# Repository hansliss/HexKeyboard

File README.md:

# HexKeyboard

A 25 x 25 keypad with a LED display and many features.

* The matrix rows are on pins 4, 12, 6, 7, 23
* The matrix columns are on pins 22, 21, 20, 19, 18

The SD card holder is connected to SPI, plus

* Card Detect = PB0 / pin 17
* Chip Enable = PB4 / pin 8

Note that CD is connected to the RXLED pin, so it will probably collide with serial data.

The display is connected like this:

* CLK = 9
* CS = 10
* DIN = 11

This requires a local max7219.h with the defines modified. Just copy 

### Serial LED pins
If you want to eliminate problems with the two LED pins (see above), you can always just disable the entire functionality, by modifying USBCore.cpp (probably found here: _C:\Users\Yourname\AppData\Local\Arduino15\packages\arduino\hardware\avr\1.8.6\cores\arduino_).

Just comment out everything to do with RXLED and TXLED, and the file will be recompiled upon the next build.

### Misc
The SPI pins for the MAX7219 display aren't actually SPI pins. Still, the max7219 library just bit-bangs the protocol so it doesn't really matter.

If you add an ESP-01/ESP-01S (with the Espressif "AT" firmware, for instance), set it to use 9600 baud
on the serial interface. The default 115200 baud seems a bit too fast.

If you print the case, and want a LED indicator for the ESP-01, print out the included wifiSign model on
a resin printer using transparent resin, then drill a 3.5mm hole roughly 3.7mm below the lower edge of the
display and 13mm to the right of the right edge of the display, insert the transparent plug, and then pour black resin carefully around the symbol (preferably using a syringe and microscope) and cure it with a UV
light.

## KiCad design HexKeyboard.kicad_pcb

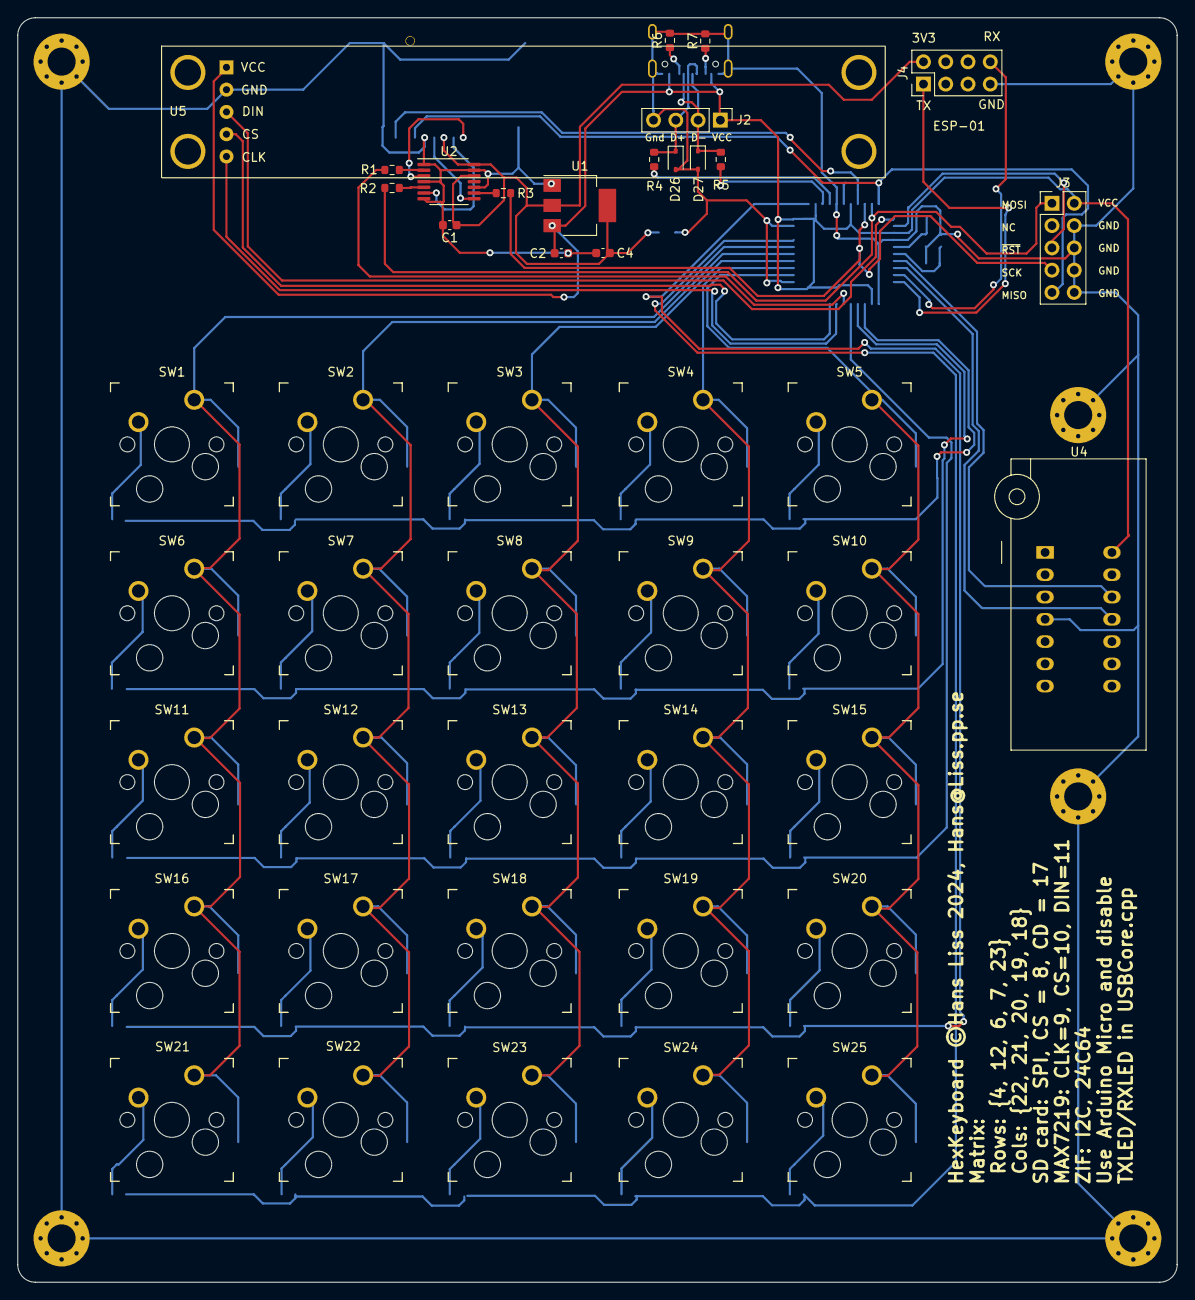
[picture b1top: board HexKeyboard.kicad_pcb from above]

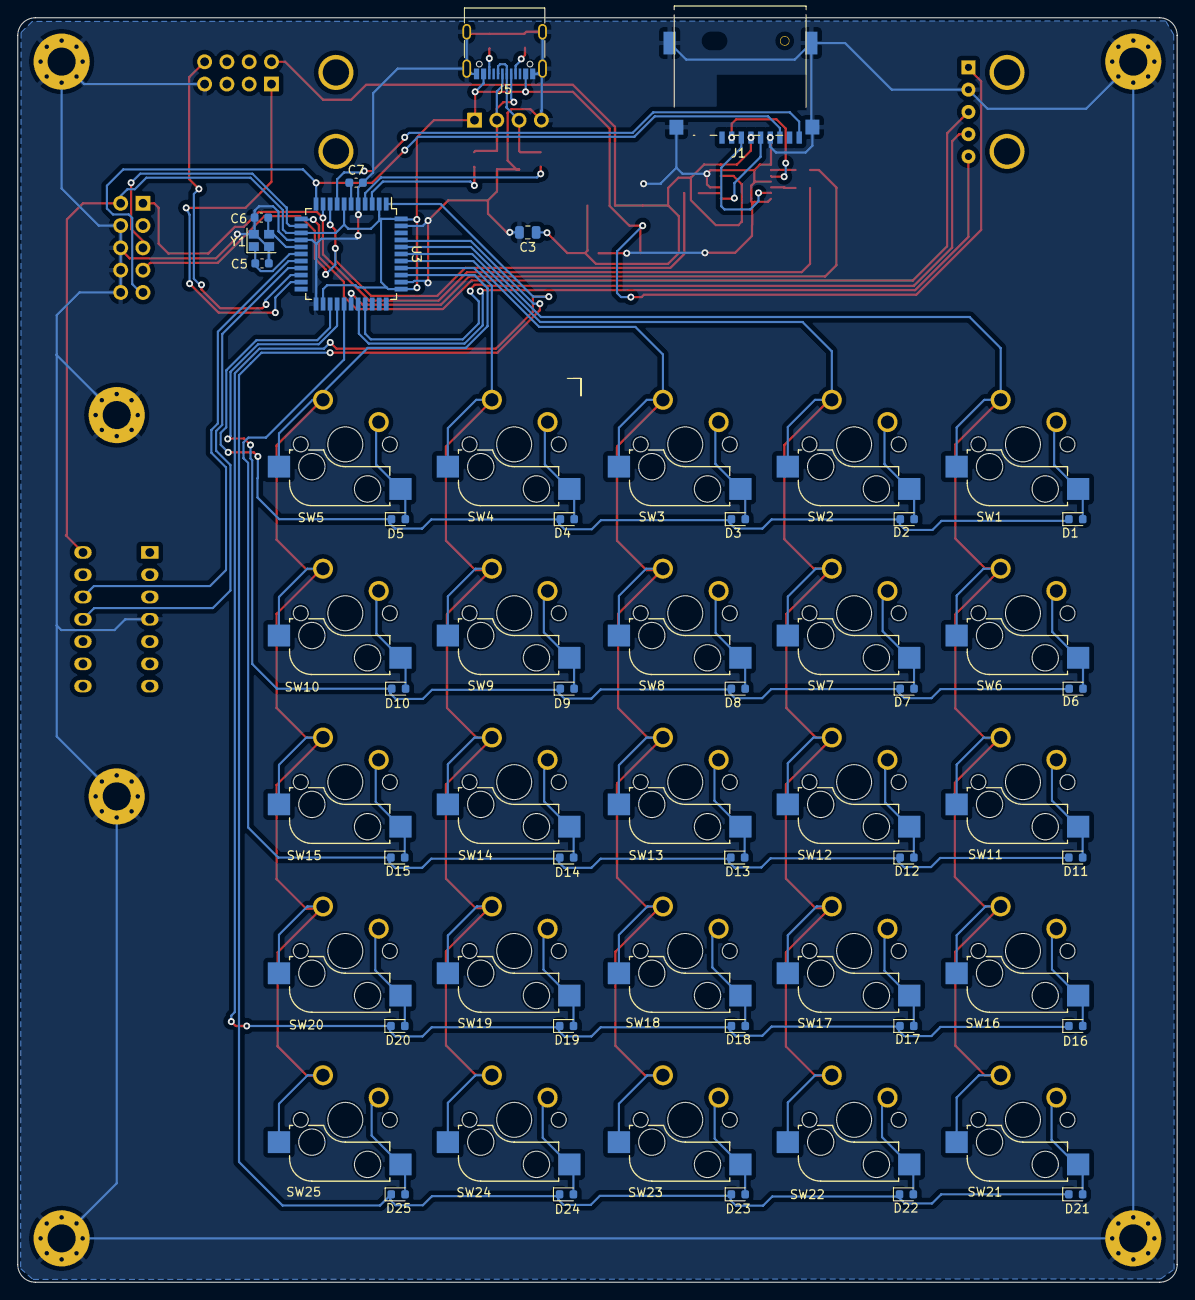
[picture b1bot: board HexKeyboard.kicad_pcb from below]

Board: 2 copper layers, 132.2 x 144.1 mm, 83 parts (33 on the bottom side), 66 nets.

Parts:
C1, C2, C4: 100nF; C_0603_1608Metric
C3: 10uF/10V; C_0805_2012Metric
C5, C6: 9pF; C_0603_1608Metric
C7: 1uF; C_0603_1608Metric
D1, D2, D3, D4, D5, D6, D7, D8, D9, D10, D11, D12, D13, D14, D15, D16, D17, D18, D19, D20, D21, D22, D23, D24, D25: D; D_0603_1608Metric
D26, D27: BZX384-xxx; D_SOD-323
H1, H2, H3, H4, H5, H6: MountingHole_Pad; MountingHole_3.2mm_M3_Pad_Via
J1: Micro_SD_Card; GCT_MEM2075
J2: Conn_01x04; PinHeader_1x04_P2.54mm_Vertical
J3: Conn_02x04_Odd_Even; PinHeader_2x05_P2.54mm_Vertical
J4: Conn_02x04_Odd_Even; PinHeader_2x04_P2.54mm_Vertical
J5: USB_A; USB_C_Receptacle_G-Switch_GT-USB-7010ASV
R1, R2, R3: 3k3; R_0603_1608Metric
R4, R5: 22; R_0603_1608Metric
R6, R7: 5k6; R_0603_1608Metric
SW1: SW_1; Kailh_socket_MX_optional_compatible
SW2: SW_2; Kailh_socket_MX_optional_compatible
SW3: SW_3; Kailh_socket_MX_optional_compatible
SW4: SW_4; Kailh_socket_MX_optional_compatible
SW5: SW_5; Kailh_socket_MX_optional_compatible
SW6: SW_6; Kailh_socket_MX_optional_compatible
SW7: SW_7; Kailh_socket_MX_optional_compatible
SW8: SW_8; Kailh_socket_MX_optional_compatible
SW9: SW_9; Kailh_socket_MX_optional_compatible
SW10: SW_10; Kailh_socket_MX_optional_compatible
SW11: SW_11; Kailh_socket_MX_optional_compatible
SW12: SW_12; Kailh_socket_MX_optional_compatible
SW13: SW_13; Kailh_socket_MX_optional_compatible
SW14: SW_14; Kailh_socket_MX_optional_compatible
SW15: SW_15; Kailh_socket_MX_optional_compatible
SW16: SW_16; Kailh_socket_MX_optional_compatible
SW17: SW_17; Kailh_socket_MX_optional_compatible
SW18: SW_18; Kailh_socket_MX_optional_compatible
SW19: SW_19; Kailh_socket_MX_optional_compatible
SW20: SW_20; Kailh_socket_MX_optional_compatible
SW21: SW_21; Kailh_socket_MX_optional_compatible
SW22: SW_22; Kailh_socket_MX_optional_compatible
SW23: SW_23; Kailh_socket_MX_optional_compatible
SW24: SW_24; Kailh_socket_MX_optional_compatible
SW25: SW_25; Kailh_socket_MX_optional_compatible
U1: AMS1117-3.3; SOT-223-3_TabPin2
U2: 74LVC125; TSSOP-14_4.4x5mm_P0.65mm
U3: ATmega32U4-AU; TQFP-44_10x10mm_P0.8mm
U4: AT24CS64-XHM; DIP_Socket-14_W4.3_W5.08_W7.62_W10.16_W10.9_3M_214-3339-00-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
U5: MAX7219; Display_x8_MAX7219
Y1: 16MHz; Crystal_SMD_2520-4Pin_2.5x2.0mm

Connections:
+3.3V: C1.1, C3.1, C4.1, J1.4 (VDD), J4.2, U1.2 (VO), U2.12, U2.14 (VCC)
/CD: J1.9 (DET), U3.8 (PB0)
/CE: R1.2, U3.28 (PB4)
/MISO: J1.7 (DAT0), J3.9, U3.11 (PB3)
/MOSI: J3.1, R2.2, U3.10 (PB2)
/RX: J4.8, U3.20 (PD2)
/SCK: J3.7, R3.2, U3.9 (PB1)
/SCL: U3.18 (PD0), U4.12 (SCL)
/SDA: U3.19 (PD1), U4.11 (SDA)
/TX: J4.1, U3.21 (PD3)
/~RESET: J3.5, U3.13 (~RESET)
COL0: SW1.1, SW6.1, SW11.1, SW16.1, SW21.1, U3.40 (PF1)
COL1: SW2.1, SW7.1, SW12.1, SW17.1, SW22.1, U3.39 (PF4)
COL2: SW3.1, SW8.1, SW13.1, SW18.1, SW23.1, U3.38 (PF5)
COL3: SW4.1, SW9.1, SW14.1, SW19.1, SW24.1, U3.37 (PF6)
COL4: SW5.1, SW10.1, SW15.1, SW20.1, SW25.1, U3.36 (PF7)
GND: C1.2, C2.2, C3.2, C4.2, C5.2, C6.2, C7.2, D26.2 (A), D27.2 (A), H1.1, H2.1, H3.1, H4.1, H5.1, H6.1, J1.6 (VSS), J1.10 (SHIELD), J2.4, J3.4, J3.6, J3.8, J3.10, J4.7, J5.A1 (GND), J5.A12 (GND), J5.B1 (GND), J5.B12 (GND), J5.S1 (SHIELD), R6.2, R7.2, U1.1 (GND), U2.1, U2.4, U2.7 (GND), U2.10, U2.13, U3.5 (UGND), U3.15 (GND), U3.23 (GND), U3.35 (GND), U3.43 (GND), U4.4 (GND), U5.2 (GND), Y1.2, Y1.4
unnamed: D1.2 (A), SW1.2
unnamed: D2.2 (A), SW2.2
unnamed: D3.2 (A), SW3.2
unnamed: D4.2 (A), SW4.2
unnamed: D5.2 (A), SW5.2
unnamed: D6.2 (A), SW6.2
unnamed: D7.2 (A), SW7.2
unnamed: D8.2 (A), SW8.2
unnamed: D9.2 (A), SW9.2
unnamed: D10.2 (A), SW10.2
unnamed: D11.2 (A), SW11.2
unnamed: D12.2 (A), SW12.2
unnamed: D13.2 (A), SW13.2
unnamed: D14.2 (A), SW14.2
unnamed: D15.2 (A), SW15.2
unnamed: D16.2 (A), SW16.2
unnamed: D17.2 (A), SW17.2
unnamed: D18.2 (A), SW18.2
unnamed: D19.2 (A), SW19.2
unnamed: D20.2 (A), SW20.2
unnamed: D21.2 (A), SW21.2
unnamed: D22.2 (A), SW22.2
unnamed: D23.2 (A), SW23.2
unnamed: D24.2 (A), SW24.2
unnamed: D25.2 (A), SW25.2
unnamed: D26.1 (K), J2.3, J5.A6 (D+), J5.B6 (D+), R4.2
unnamed: D27.1 (K), J2.2, J5.A7 (D-), J5.B7 (D-), R5.2
unnamed: J1.5 (CLK), U2.8
unnamed: J1.3 (CMD), U2.6
unnamed: J1.2 (DAT3/CD), U2.3
unnamed: J5.A5 (CC1), R6.1
unnamed: J5.B5 (CC2), R7.1
unnamed: R1.1, U2.2
unnamed: R2.1, U2.5
unnamed: R3.1, U2.9
unnamed: R4.1, U3.4 (D+)
unnamed: R5.1, U3.3 (D-)
unnamed: U3.29 (PB5), U5.5 (CLK)
unnamed: U3.30 (PB6), U5.4 (CS)
unnamed: U3.12 (PB7), U5.3 (DIN)
unnamed: C7.1, U3.6 (UCAP)
unnamed: C5.1, U3.17 (XTAL1), Y1.1
unnamed: C6.1, U3.16 (XTAL2), Y1.3
ROW0: D1.1 (K), D2.1 (K), D3.1 (K), D4.1 (K), D5.1 (K), U3.25 (PD4)
ROW1: D6.1 (K), D7.1 (K), D8.1 (K), D9.1 (K), D10.1 (K), U3.26 (PD6)
ROW2: D11.1 (K), D12.1 (K), D13.1 (K), D14.1 (K), D15.1 (K), U3.27 (PD7)
ROW3: D16.1 (K), D17.1 (K), D18.1 (K), D19.1 (K), D20.1 (K), U3.1 (PE6)
ROW4: D21.1 (K), D22.1 (K), D23.1 (K), D24.1 (K), D25.1 (K), U3.41 (PF0)
VCC: C2.1, J2.1, J3.2, J5.A4 (VBUS), J5.A9 (VBUS), J5.B4 (VBUS), J5.B9 (VBUS), U1.3 (VI), U3.2 (UVCC), U3.7 (VBUS), U3.14 (VCC), U3.24 (AVCC), U3.34 (VCC), U3.44 (AVCC), U4.14 (VCC), U5.1 (VCC)

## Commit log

2024-04-25 Initial import
2024-04-25 Cleaned up libraries Added Display Switched to USB-C
2024-04-25 Filled up matrix to 5x5 Started on layout
2024-04-25 Finished layout and routing
2024-04-25 Connected mounting holes to Gnd Added filled zone
2024-04-25 Switched to the correct MicroSD holder
2024-05-01 Moved datasheets to Docs/ Added simple sketch to test display, keyboard, basic HID code etc. Added some documentation in README.md Added Gerbers for first prototype
2024-05-01 Reorganized the code to handle the timing better Added a hex keypress queue Added basic formatted hex output - on Serial port for now.
2024-05-01 Added photo
2024-05-06 Footprint for SD holder updated. SD holder turned 180 deg USB connector moved out a bit
2024-05-07 Added serial port. Added new pin numbers to sketch
2024-05-08 Added a faceplate for the hotswap switches.
2024-05-11 Complete rudimentary case design added
2024-05-11 Removed unwanted files from repo
2024-05-11 Removed more files from repo
2024-05-11 Updated README.md with new row pins
2024-05-11 Minor cleanup of the scad files. .gitignore and cleanup of files
2024-05-11 Added backup directory to .gitignore
2024-05-16 Fixed some erroneous pin numbers
2024-05-19 Added a slanted platform to the case bottom, for holding a damper against the back of the keypad. Added a comment about ESP-01 communication
2024-05-20 Initial WiFi code Remove Strings Cleaned up unused stuff
2024-05-20 Better reading of configuration files
2024-05-25 New case models
2024-05-29 Added more info to the README.md Added wifiSign 3d model
2024-05-31 Changed the case to fix the margins around the PCB.
2024-05-31 Scaled down the photo and added a second photo
2024-05-31 Added a short description to the README

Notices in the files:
HexKeyboard.kicad_pcb:
HexKeyboard ©Hans Liss 2024, Hans@Liss.pp.se
